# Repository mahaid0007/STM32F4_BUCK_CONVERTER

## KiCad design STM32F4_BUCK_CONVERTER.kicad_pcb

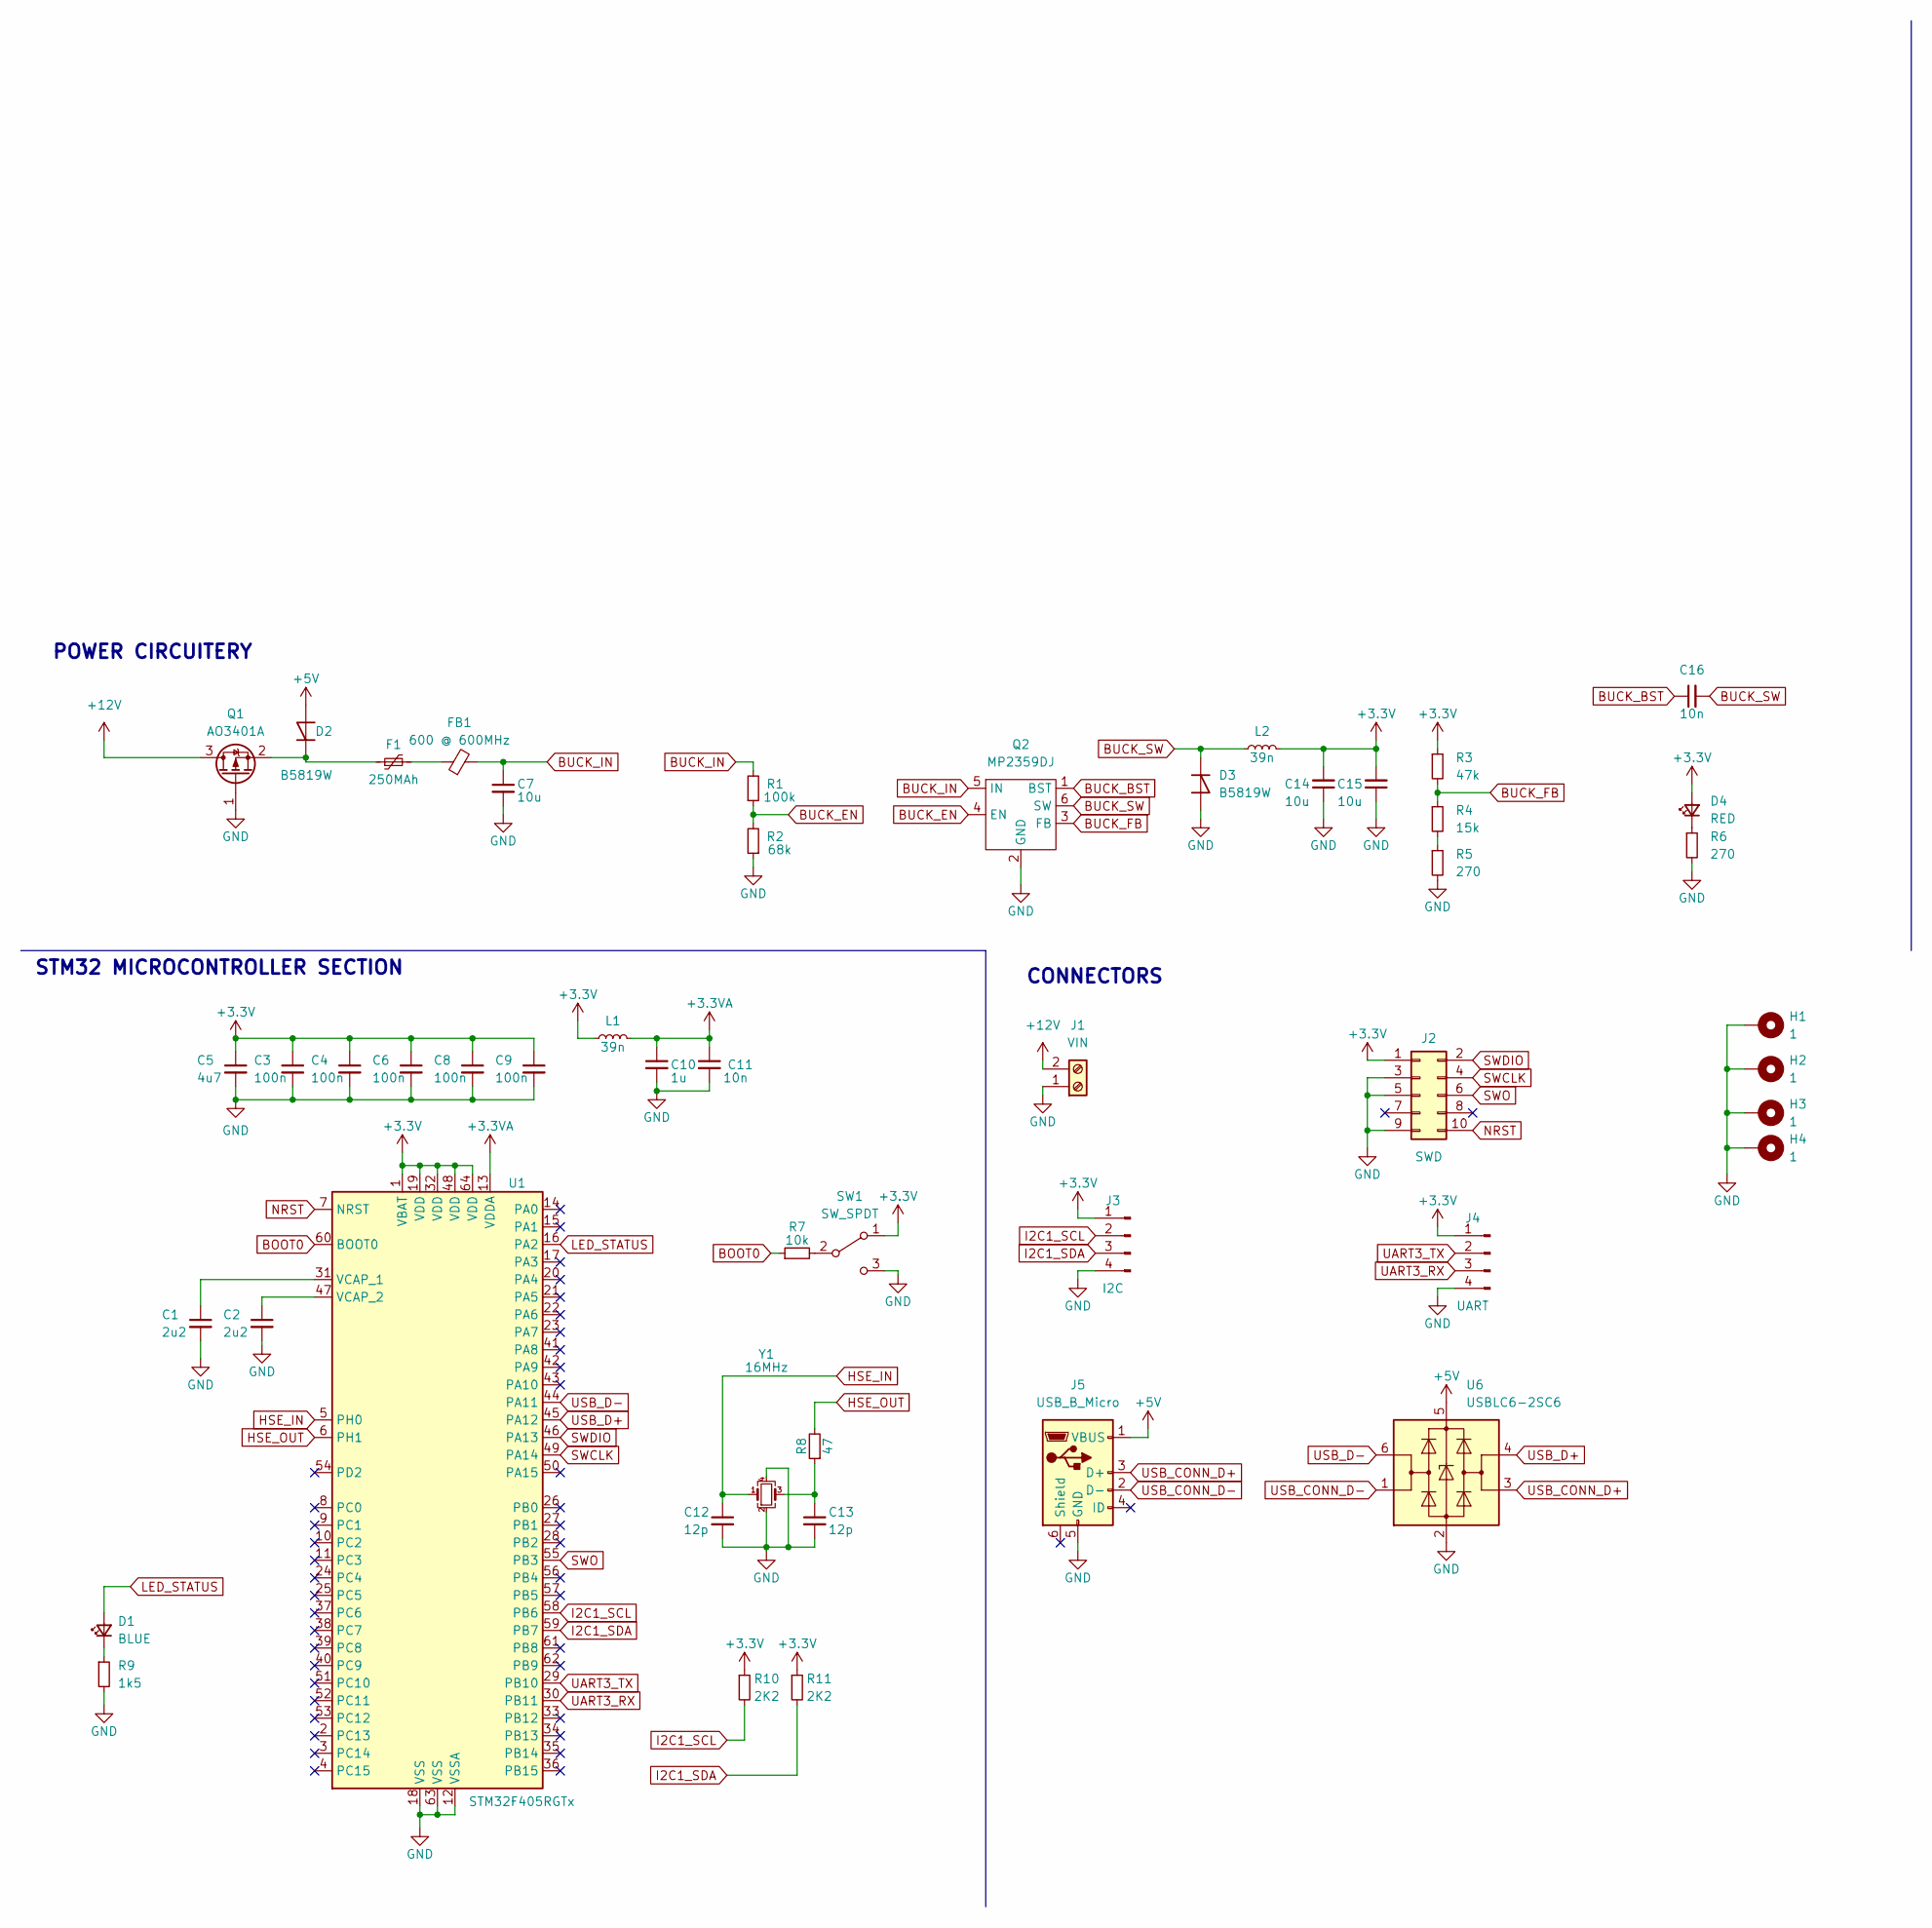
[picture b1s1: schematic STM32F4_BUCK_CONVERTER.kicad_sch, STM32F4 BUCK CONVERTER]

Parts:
C1, C2: 2u2; C_0603_1608Metric
C3, C4, C6, C8, C9: 100n; C_0603_1608Metric
C5: 4u7; C_0603_1608Metric
C7, C14, C15: 10u; C_0603_1608Metric
C10: 1u; C_0603_1608Metric
C11, C16: 10n; C_0603_1608Metric
C12, C13: 12p; C_0603_1608Metric
D1: BLUE; LED_0805_2012Metric
D2, D3: B5819W; D_SOD-123
D4: RED; LED_0805_2012Metric
F1: 250MAh; Fuse_1206_3216Metric
FB1: 600 @ 600MHz; L_1206_3216Metric
H1, H2, H3, H4: 1; MountingHole_2.5mm_Pad_Via
J1: VIN; TerminalBlock_Phoenix_PT-1,5-2-3.5-H_1x02_P3.50mm_Horizontal
J2: SWD; PinSocket_2x05_P1.27mm_Vertical_SMD
J3: I2C; Molex_PicoBlade_53048-0410_1x04_P1.25mm_Horizontal
J4: UART; Molex_PicoBlade_53048-0410_1x04_P1.25mm_Horizontal
J5: USB_B_Micro; USB_Micro-B_Amphenol_10104110_Horizontal
L1: 39n; L_0805_2012Metric
L2: 39n; L_1008_2520Metric
Q1: AO3401A; SOT-23
Q2: MP2359DJ; SOT-23-6
R1: 100k; R_0603_1608Metric
R2: 68k; R_0603_1608Metric
R3: 47k; R_0603_1608Metric
R4: 15k; R_0603_1608Metric
R5, R6: 270; R_0603_1608Metric
R7: 10k; R_0603_1608Metric
R8: 47; R_0603_1608Metric
R9: 1k5; R_0603_1608Metric
R10, R11: 2K2; R_0603_1608Metric
SW1: SW_SPDT; SW_SPDT_PCM12
U1: STM32F405RGTx; LQFP-64_10x10mm_P0.5mm
U6: USBLC6-2SC6; SOT-23-6
Y1: 16MHz; Crystal_SMD_3225-4Pin_3.2x2.5mm

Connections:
+3.3V: C3.1, C4.1, C5.1, C6.1, C8.1, C9.1, C14.2, C15.2, D4.2 (A), J2.1, J3.1, J4.1, L1.1, L2.2, R3.1, R10.1, R11.1, SW1.1 (A), U1.1 (VBAT), U1.19 (VDD), U1.32 (VDD), U1.48 (VDD), U1.64 (VDD)
+3.3VA: C10.1, C11.1, L1.2, U1.13 (VDDA)
+5V: D2.2 (A), J5.1 (VBUS), U6.5 (VBUS)
+12V: J1.2, Q1.3 (D)
BOOT0: R7.1, U1.60 (BOOT0)
BUCK_BST: C16.1, Q2.1 (BST)
BUCK_FB: Q2.3 (FB), R3.2, R4.1
BUCK_IN: C7.1, FB1.2, Q2.5 (IN), R1.2
BUCK_OUT: Q2.4 (EN), R1.1, R2.2
BUCK_SW: C16.2, D3.1 (K), L2.1, Q2.6 (SW)
GND: C1.2, C2.2, C3.2, C4.2, C5.2, C6.2, C7.2, C8.2, C9.2, C10.2, C11.2, C12.2, C13.2, C14.1, C15.1, D3.2 (A), H1.1, H2.1, H3.1, H4.1, J1.1, J2.3, J2.5, J2.9, J3.4, J4.4, J5.5 (GND), Q1.1 (G), Q2.2 (GND), R2.1, R5.2, R6.2, R9.2, SW1.3 (C), U1.12 (VSSA), U1.18 (VSS), U1.63 (VSS), U6.2 (GND), Y1.2, Y1.4
HSE_IN: C12.1, U1.5 (PH0), Y1.1
HSE_OUT: R8.2, U1.6 (PH1)
I2C1_SCL: J3.2, R10.2, U1.58 (PB6)
I2C1_SDA: J3.3, R11.2, U1.59 (PB7)
LED_STATUS: D1.2 (A), U1.16 (PA2)
NRST: J2.10, U1.7 (NRST)
unnamed: C1.1, U1.31 (VCAP_1)
unnamed: C2.1, U1.47 (VCAP_2)
unnamed: C13.1, R8.1, Y1.3
unnamed: D1.1 (K), R9.1
unnamed: D2.1 (K), F1.1, Q1.2 (S)
unnamed: D4.1 (K), R6.1
unnamed: F1.2, FB1.1
unnamed: R4.2, R5.1
unnamed: R7.2, SW1.2 (B)
SWCLK: J2.4, U1.49 (PA14)
SWDIO: J2.2, U1.46 (PA13)
SWO: J2.6, U1.55 (PB3)
UART3_RX: J4.3, U1.30 (PB11)
UART3_TX: J4.2, U1.29 (PB10)
USB_CONN_D+: J5.3 (D+), U6.3 (I/O2)
USB_CONN_D-: J5.2 (D-), U6.1 (I/O1)
USB_D+: U1.45 (PA12), U6.4 (I/O2)
USB_D-: U1.44 (PA11), U6.6 (I/O1)

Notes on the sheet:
CONNECTORS
STM32 MICROCONTROLLER SECTION
POWER CIRCUITERY

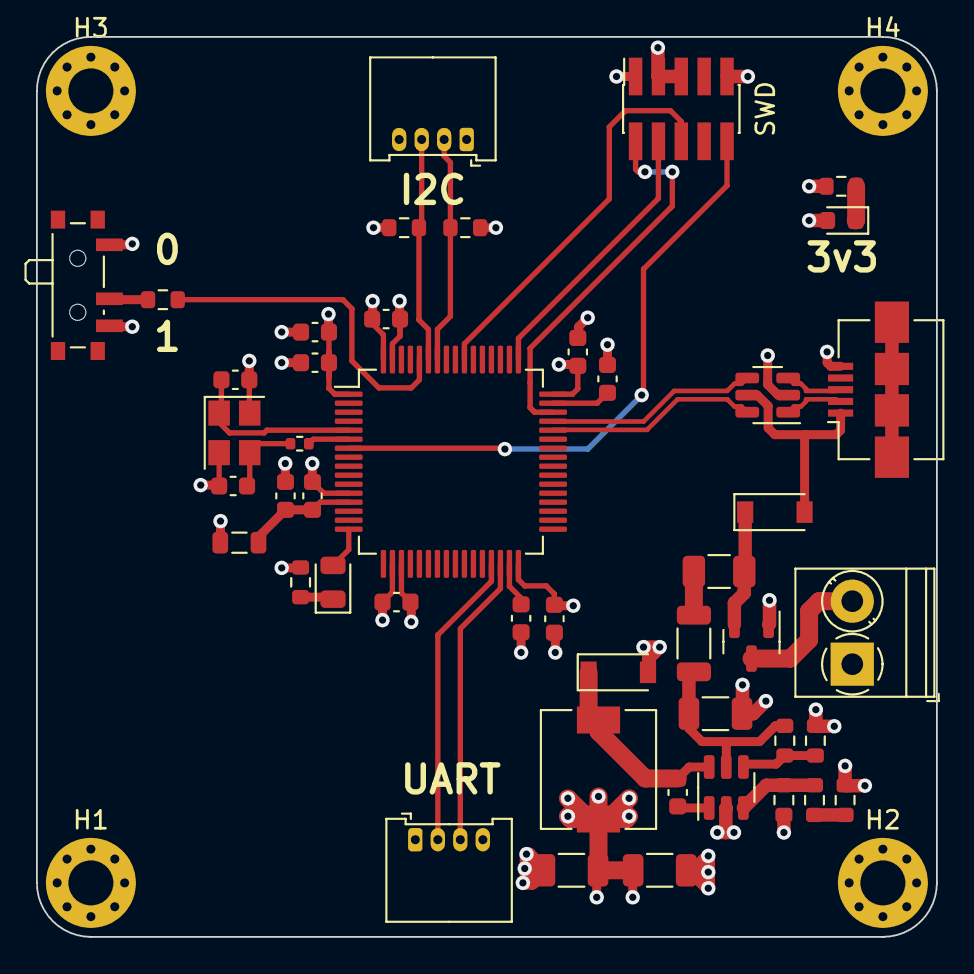
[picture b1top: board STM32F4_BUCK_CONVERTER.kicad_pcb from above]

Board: 4 copper layers, 50.0 x 50.0 mm, 50 parts (0 on the bottom side), 35 nets.

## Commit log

2023-03-22 stm32f4 breakout board with buck converter
